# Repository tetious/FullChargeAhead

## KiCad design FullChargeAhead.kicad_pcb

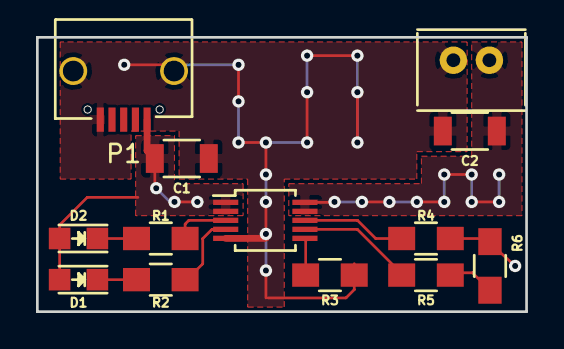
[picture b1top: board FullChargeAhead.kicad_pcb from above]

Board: 2 copper layers, 27.2 x 15.2 mm, 13 parts (0 on the bottom side), 11 nets.

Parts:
C1, C2: 4.7u; C_1206
D1, D2: LED; LED_0805
P1: USB_PWR; USB_Micro-B-ebay
P2: BATT; B2B-PH-K-S
R1, R2: 470; R_0805_HandSoldering
R3: 2k; R_0805_HandSoldering
R4: 10k; R_0805_HandSoldering
R5: 1k; R_0805_HandSoldering
R6: R; R_0805_HandSoldering
U1: MCP73834-FCI/UN; MSOP-10_3x3mm_Pitch0.5mm

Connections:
/Vin: C1.1, D1.2, D2.2, P1.1, U1.1, U1.2
/Vout: C2.1, P2.1, U1.9, U1.10
GND: C1.2, C2.2, P1.5, P1.6, P2.2, R3.2, R4.2, R6.2, U1.5
unnamed: D1.1, R2.2
unnamed: D2.1, R1.2
unnamed: R1.1, U1.3
unnamed: R2.1, U1.4
unnamed: R3.1, U1.6
unnamed: R4.1, U1.8
unnamed: R5.1, U1.7
unnamed: R5.2, R6.1

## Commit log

2016-07-22 Initial checkin.
2016-07-22 Update footprints.
2016-07-23 Final v1 board.
2016-07-23 Add BOM.
2016-08-12 Fix USB footprint.
